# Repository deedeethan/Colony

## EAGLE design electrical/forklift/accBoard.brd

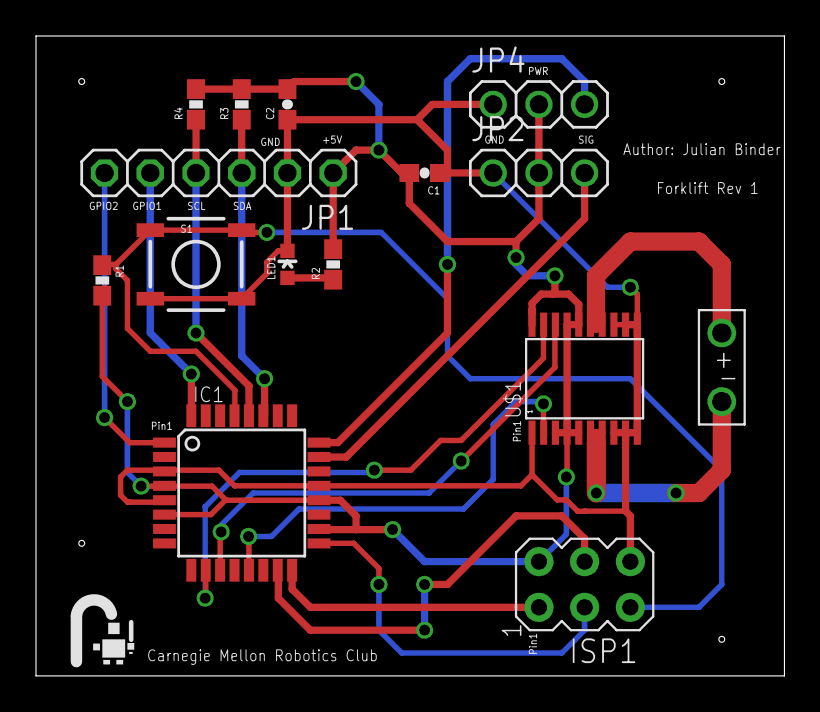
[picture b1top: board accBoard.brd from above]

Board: 2 copper layers, 41.6 x 35.6 mm, 15 parts (0 on the bottom side), 18 nets.

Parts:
C1: 0.1uF; 0603-CAP
C2: 0.1uf; 0603-CAP
IC1: MEGA168; TQFP32-08
ISP1: AVRISP-6; AVRISP
JP1: 1X06
JP2, JP4: 1X03
JP3: 1X02_BIG
LED1: GREENLED; LED-0603
R1, R3, R4: 10K; 0603-RES
R2: 330; 0603-RES
S1: TACTILE_SWITCH_SMD
U$1: TB6593FNG; SSOP20

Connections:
AVR_MISO: IC1.16, ISP1.1
AVR_MOSI: IC1.15, ISP1.4
AVR_RST: IC1.29, ISP1.5, R1.1, S1.1, S1.2
AVR_SCK: IC1.17, ISP1.3
EXTRA_SIG: IC1.24, JP4.3
GND: C1.1, C2.1, IC1.3, IC1.5, IC1.21, ISP1.6, JP1.2, JP2.1, JP4.1, LED1.C, S1.3, S1.4, U$1.1, U$1.8, U$1.9, U$1.10, U$1.11, U$1.12, U$1.13
GPIO1: IC1.32, JP1.5
GPIO2: IC1.1, JP1.6
IN1: IC1.11, U$1.18
IN2: IC1.10, U$1.19
unnamed: LED1.A, R2.1
O1: JP3.P$1, U$1.6, U$1.7
O2: JP3.P$2, U$1.14, U$1.15
POT_SIG: IC1.23, JP2.3
PWM: IC1.13, U$1.2
SCL: IC1.28, JP1.4, R4.1
SDA: IC1.27, JP1.3, R3.1
VCC: C1.2, C2.2, IC1.4, IC1.6, IC1.18, IC1.20, ISP1.2, JP1.1, JP2.2, JP4.2, R1.2, R2.2, R3.2, R4.2, U$1.3, U$1.4, U$1.5, U$1.16, U$1.17, U$1.20

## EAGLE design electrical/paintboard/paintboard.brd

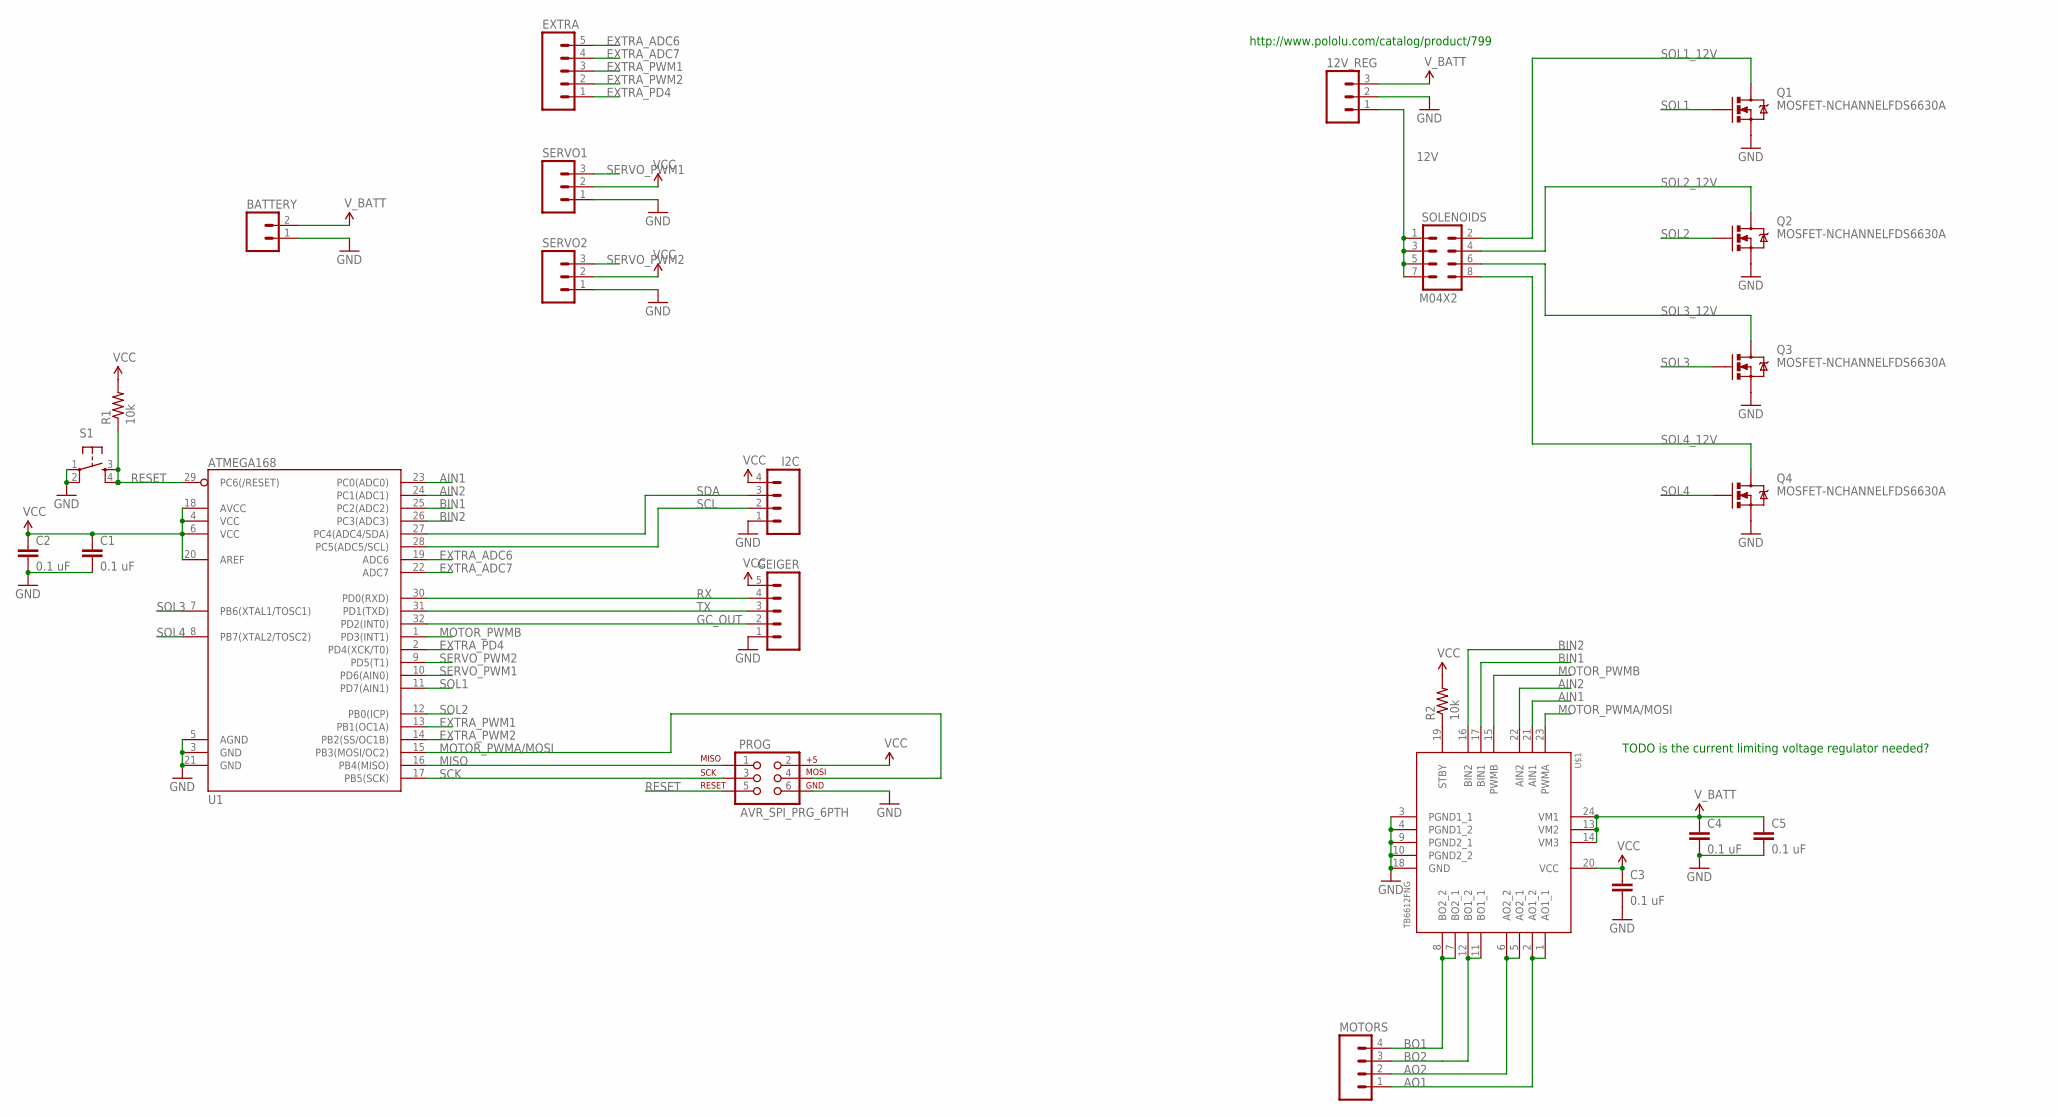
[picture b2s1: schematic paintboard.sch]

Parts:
12V_REG: M03PTH; 1X03
BATTERY: M02PTH; 1X02
C1, C2, C3, C4, C5: 0.1 uF; 0805
EXTRA: M05PTH; 1X05
GEIGER: M05PTH; 1X05
I2C: M04PTH; 1X04
MOTORS: M04PTH; 1X04
PROG: AVR_SPI_PRG_6PTH; 2X3
Q1, Q2, Q3, Q4: MOSFET-NCHANNELFDS6630A; SO08
R1, R2: 10k; 0805
S1: TAC_SWITCHSMD; TACTILE_SWITCH_SMD
SERVO1, SERVO2: M03PTH; 1X03
SOLENOIDS: M04X2; 2X4
U1: ATMEGA168; TQFP32-08
U$1: TB6612FNG; 24-SSOP

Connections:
12V: 12V_REG.1, SOLENOIDS.1, SOLENOIDS.3, SOLENOIDS.5, SOLENOIDS.7
AIN1: U1.23 (PC0(ADC0)), U$1.21 (AIN1)
AIN2: U1.24 (PC1(ADC1)), U$1.22 (AIN2)
AO1: MOTORS.1, U$1.1 (AO1_1), U$1.2 (AO1_2)
AO2: MOTORS.2, U$1.5 (AO2_1), U$1.6 (AO2_2)
BIN1: U1.25 (PC2(ADC2)), U$1.17 (BIN1)
BIN2: U1.26 (PC3(ADC3)), U$1.16 (BIN2)
BO1: MOTORS.4, U$1.7 (BO2_1), U$1.8 (BO2_2)
BO2: MOTORS.3, U$1.11 (BO1_1), U$1.12 (BO1_2)
EXTRA_ADC6: EXTRA.5, U1.19 (ADC6)
EXTRA_ADC7: EXTRA.4, U1.22 (ADC7)
EXTRA_PD4: EXTRA.1, U1.2 (PD4(XCK/T0))
EXTRA_PWM1: EXTRA.3, U1.13 (PB1(OC1A))
EXTRA_PWM2: EXTRA.2, U1.14 (PB2(SS/OC1B))
GC_OUT: GEIGER.2, U1.32 (PD2(INT0))
GND: 12V_REG.2, BATTERY.1, C1.2, C2.2, C3.2, C4.2, C5.2, GEIGER.1, I2C.1, PROG.6, Q1.1 (S), Q1.2 (S), Q1.3 (S), Q2.1 (S), Q2.2 (S), Q2.3 (S), Q3.1 (S), Q3.2 (S), Q3.3 (S), Q4.1 (S), Q4.2 (S), Q4.3 (S), S1.1, S1.2, SERVO1.1, SERVO2.1, U1.3 (GND), U1.5 (AGND), U1.21 (GND), U$1.3 (PGND1_1), U$1.4 (PGND1_2), U$1.9 (PGND2_1), U$1.10 (PGND2_2), U$1.18 (GND)
MISO: PROG.1, U1.16 (PB4(MISO))
MOTOR_PWMA/MOSI: PROG.4, U1.15 (PB3(MOSI/OC2)), U$1.23 (PWMA)
MOTOR_PWMB: U1.1 (PD3(INT1)), U$1.15 (PWMB)
unnamed: R2.1, U$1.19 (STBY)
RESET: PROG.5, R1.1, S1.3, S1.4, U1.29 (PC6(/RESET))
RX: GEIGER.4, U1.30 (PD0(RXD))
SCK: PROG.3, U1.17 (PB5(SCK))
SCL: I2C.2, U1.28 (PC5(ADC5/SCL))
SDA: I2C.3, U1.27 (PC4(ADC4/SDA))
SERVO_PWM1: SERVO1.3, U1.10 (PD6(AIN0))
SERVO_PWM2: SERVO2.3, U1.9 (PD5(T1))
SOL1: Q1.4 (G), U1.11 (PD7(AIN1))
SOL1_12V: Q1.5 (D), Q1.6 (D), Q1.7 (D), Q1.8 (D), SOLENOIDS.2
SOL2: Q2.4 (G), U1.12 (PB0(ICP))
SOL2_12V: Q2.5 (D), Q2.6 (D), Q2.7 (D), Q2.8 (D), SOLENOIDS.4
SOL3: Q3.4 (G), U1.7 (PB6(XTAL1/TOSC1))
SOL3_12V: Q3.5 (D), Q3.6 (D), Q3.7 (D), Q3.8 (D), SOLENOIDS.6
SOL4: Q4.4 (G), U1.8 (PB7(XTAL2/TOSC2))
SOL4_12V: Q4.5 (D), Q4.6 (D), Q4.7 (D), Q4.8 (D), SOLENOIDS.8
TX: GEIGER.3, U1.31 (PD1(TXD))
VCC: C1.1, C2.1, C3.1, GEIGER.5, I2C.4, PROG.2, R1.2, R2.2, SERVO1.2, SERVO2.2, U1.4 (VCC), U1.6 (VCC), U1.18 (AVCC), U1.20 (AREF), U$1.20 (VCC)
V_BATT: 12V_REG.3, BATTERY.2, C4.1, C5.1, U$1.13 (VM2), U$1.14 (VM3), U$1.24 (VM1)

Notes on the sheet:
http://www.pololu.com/catalog/product/799
TODO is the current limiting voltage regulator needed?

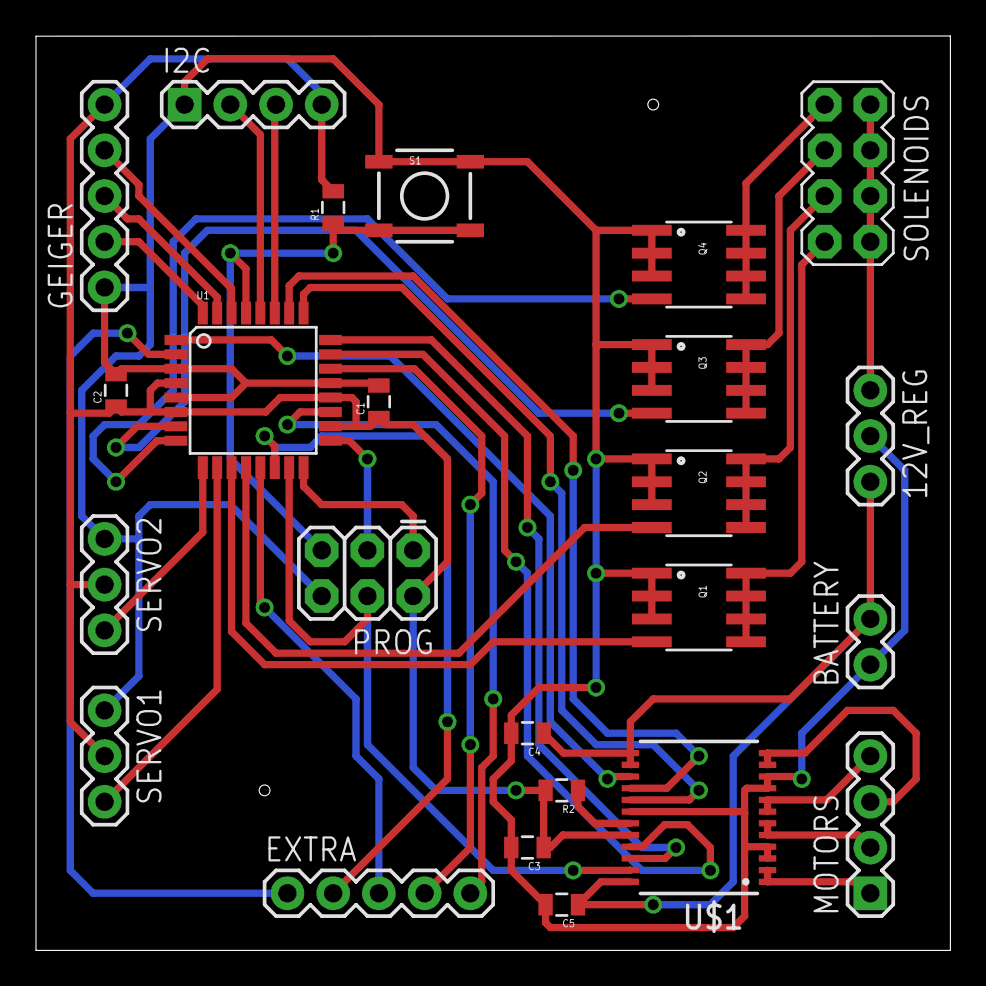
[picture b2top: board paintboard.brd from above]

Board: 2 copper layers, 50.8 x 50.8 mm, 24 parts (0 on the bottom side), 38 nets.

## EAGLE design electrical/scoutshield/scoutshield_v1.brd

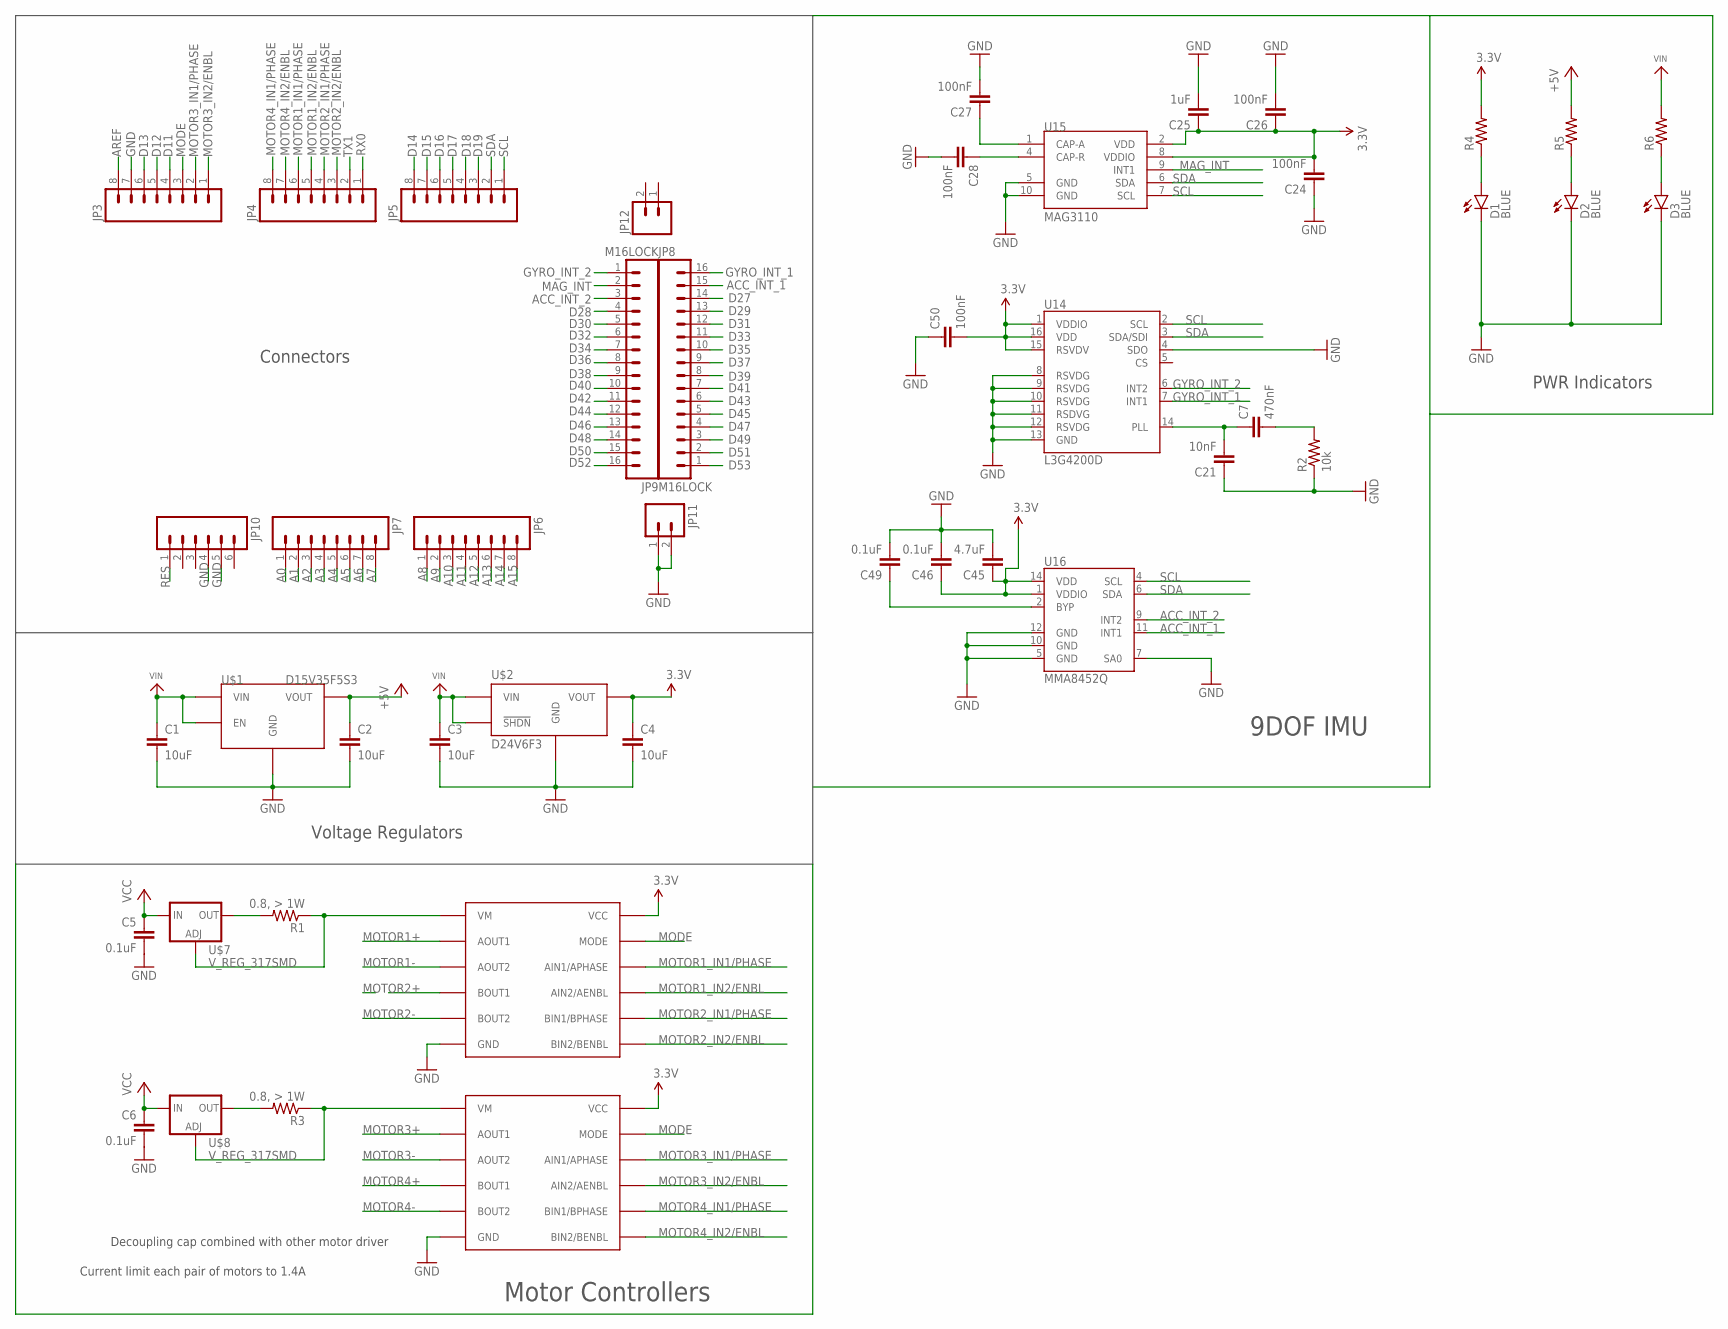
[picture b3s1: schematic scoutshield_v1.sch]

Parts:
C1, C2, C3, C4: 10uF; 1206
C5, C6, C46, C49: 0.1uF; 0603-CAP
C7: 470nF; 0603-CAP
C21: 10nF; 0603-CAP
C24, C26, C27, C28, C50: 100nF; 0603-CAP
C25: 1uF; 0603-CAP
C45: 4.7uF; 0603-CAP
D1, D2, D3: BLUE; LED-0603
JP3, JP4, JP5, JP6, JP7: M08LOCK; 1X08_LOCK
JP8, JP9: M16LOCK; 1X16_LOCK
JP10: M06LOCK; 1X06_LOCK
JP11, JP12: M02LOCK; 1X02_LOCK
R1, R3: 0.8, > 1W; R2512
R2: 10k; R0603
R4, R5, R6: RESISTOR0603-RES; 0603-RES
U14: L3G4200D; LGA16-4X4
U15: MAG3110; DFN-10
U16: MMA8452Q; QFN-16_0.5MM
U$1: D15V35F5S3
U$2: D24V6F3
U$5, U$6: DRV8835; WSON-12
U$7, U$8: V_REG_317SMD; SOT223

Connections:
3.3V: C4.1, C24.2, C25.1, C26.1, C45.1, C46.1, C50.2, R4.2, U14.1 (VDDIO), U14.15 (RSVDV), U14.16 (VDD), U15.2 (VDD), U15.8 (VDDIO), U16.1 (VDDIO), U16.14 (VDD), U$2.VOUT, U$5.P12 (VCC), U$6.P12 (VCC)
+5V: C2.1, R5.2, U$1.VOUT
A0: JP7.1
A1: JP7.2
A2: JP7.3
A3: JP7.4
A4: JP7.5
A5: JP7.6
A6: JP7.7
A7: JP7.8
A8: JP6.1
A9: JP6.2
A10: JP6.3
A11: JP6.4
A12: JP6.5
A13: JP6.6
A14: JP6.7
A15: JP6.8
ACC_INT_1: JP8.15, U16.11 (INT1)
ACC_INT_2: JP9.3, U16.9 (INT2)
AREF: JP3.8
D11: JP3.4
D12: JP3.5
D13: JP3.6
D14: JP5.8
D15: JP5.7
D16: JP5.6
D17: JP5.5
D18: JP5.4
D19: JP5.3
D27: JP8.14
D28: JP9.4
D29: JP8.13
D30: JP9.5
D31: JP8.12
D32: JP9.6
D33: JP8.11
D34: JP9.7
D35: JP8.10
D36: JP9.8
D37: JP8.9
D38: JP9.9
D39: JP8.8
D40: JP9.10
D41: JP8.7
D42: JP9.11
D43: JP8.6
D44: JP9.12
D45: JP8.5
D46: JP9.13
D47: JP8.4
D48: JP9.14
D49: JP8.3
D50: JP9.15
D51: JP8.2
D52: JP9.16
D53: JP8.1
GND: C1.2, C2.2, C3.2, C4.2, C5.2, C6.2, C21.1, C24.1, C25.2, C26.2, C27.2, C28.2, C45.2, C46.2, C49.2, C50.1, D1.C, D2.C, D3.C, JP3.7, JP10.4, JP10.5, JP11.1, JP11.2, R2.1, U14.4 (SDO), U14.8 (RSVDG), U14.9 (RSVDG), U14.10 (RSVDG), U14.11 (RSDVG), U14.12 (RSVDG), U14.13 (GND), U15.5 (GND), U15.10 (GND), U16.5 (GND), U16.7 (SA0), U16.10 (GND), U16.12 (GND), U$1.GND1 (GND), U$1.GND2 (GND), U$2.GND, U$5.P6 (GND), U$5.THERM1 (GND), U$5.THERM2 (GND), U$5.THERM3 (GND), U$5.THERM4 (GND), U$5.THERMCENTER (GND), U$6.P6 (GND), U$6.THERM1 (GND), U$6.THERM2 (GND), U$6.THERM3 (GND), U$6.THERM4 (GND), U$6.THERMCENTER (GND)
GYRO_INT_1: JP8.16, U14.7 (INT1)
GYRO_INT_2: JP9.1, U14.6 (INT2)
MAG_INT: JP9.2, U15.9 (INT1)
MODE: JP3.3, U$5.P11 (MODE), U$6.P11 (MODE)
MOTOR1+: U$6.P2 (AOUT1)
MOTOR1-: U$6.P3 (AOUT2)
MOTOR1_IN1/PHASE: JP4.6, U$6.P10 (AIN1/APHASE)
MOTOR1_IN2/ENBL: JP4.5, U$6.P9 (AIN2/AENBL)
MOTOR2+: U$6.P4 (BOUT1)
MOTOR2-: U$6.P5 (BOUT2)
MOTOR2_IN1/PHASE: JP4.4, U$6.P8 (BIN1/BPHASE)
MOTOR2_IN2/ENBL: JP4.3, U$6.P7 (BIN2/BENBL)
MOTOR3+: U$5.P2 (AOUT1)
MOTOR3-: U$5.P3 (AOUT2)
MOTOR3_IN1/PHASE: JP3.2, U$5.P10 (AIN1/APHASE)
MOTOR3_IN2/ENBL: JP3.1, U$5.P9 (AIN2/AENBL)
MOTOR4+: U$5.P4 (BOUT1)
MOTOR4-: U$5.P5 (BOUT2)
MOTOR4_IN1/PHASE: JP4.8, U$5.P8 (BIN1/BPHASE)
MOTOR4_IN2/ENBL: JP4.7, U$5.P7 (BIN2/BENBL)
unnamed: R1.1, U$6.P1 (VM), U$7.1 (ADJ)
unnamed: R1.2, U$7.2 (OUT)
unnamed: R3.1, U$5.P1 (VM), U$8.1 (ADJ)
unnamed: R3.2, U$8.2 (OUT)
unnamed: D1.A, R4.1
unnamed: D2.A, R5.1
unnamed: D3.A, R6.1
unnamed: C7.1, C21.2, U14.14 (PLL)
unnamed: C7.2, R2.2
unnamed: C49.1, U16.2 (BYP)
unnamed: C27.1, U15.1 (CAP-A)
unnamed: C28.1, U15.4 (CAP-R)
RES: JP10.1
RX0: JP4.1
SCL: JP5.1, U14.2 (SCL), U15.7 (SCL), U16.4 (SCL)
SDA: JP5.2, U14.3 (SDA/SDI), U15.6 (SDA), U16.6 (SDA)
TX1: JP4.2
VIN: C1.1, C3.1, C5.1, C6.1, R6.2, U$1.EN, U$1.VIN, U$2.!SHDN, U$2.VIN, U$7.3 (IN), U$8.3 (IN)

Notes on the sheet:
Connectors
Voltage Regulators
9DOF IMU
Decoupling cap combined with other motor driver
Current limit each pair of motors to 1.4A
Motor Controllers
PWR Indicators

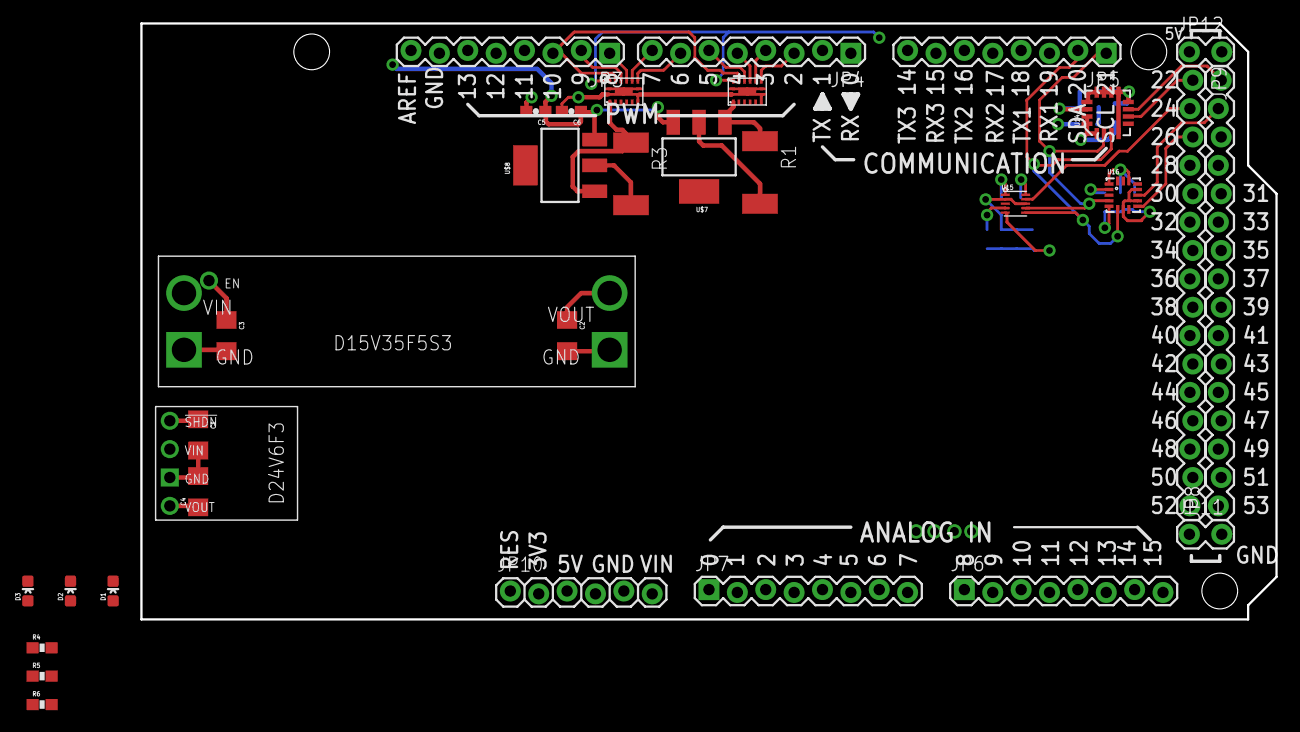
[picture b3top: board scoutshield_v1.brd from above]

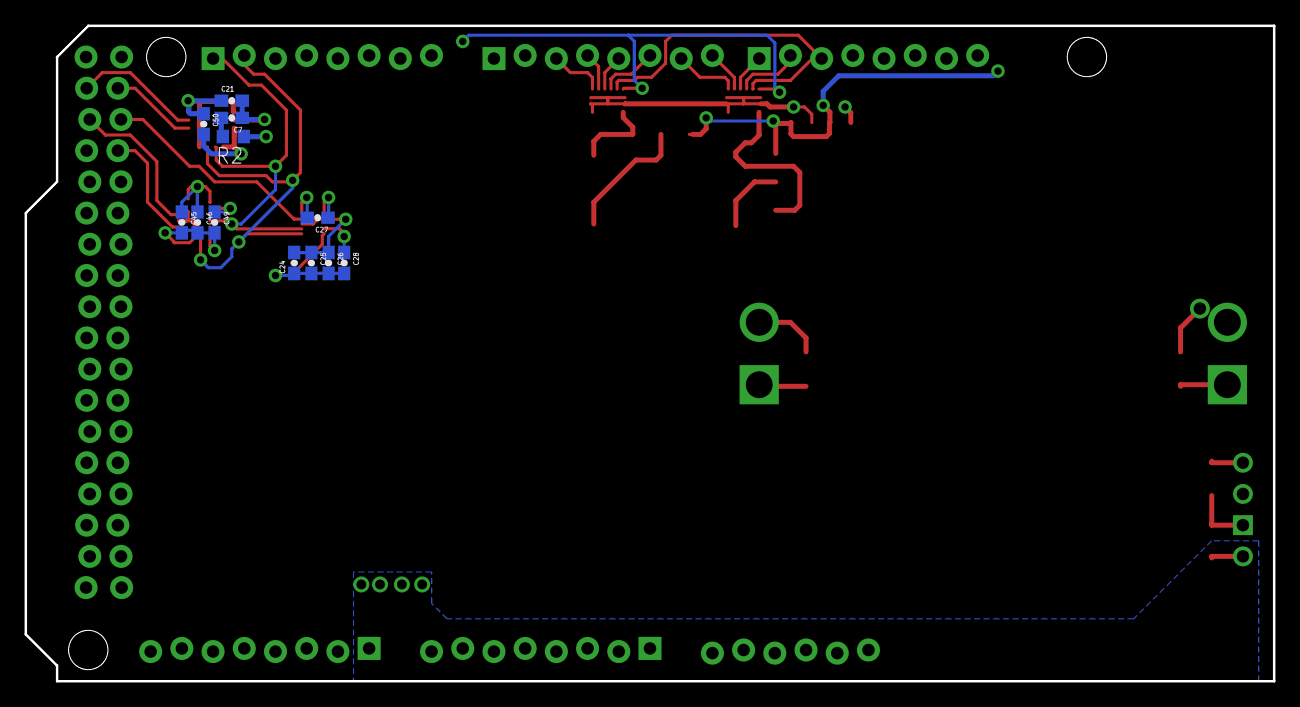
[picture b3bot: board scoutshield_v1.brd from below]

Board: 4 copper layers, 101.6 x 53.3 mm, 45 parts (12 on the bottom side), 32 nets.

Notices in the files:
parts and their libraries:
SparkFun-DigitalIC: Licensing: CC v3.0 Share-Alike You are welcome to use this library for commercial purposes.
SparkFun-LED: Licensing: Creative Commons ShareAlike 4.0 International - https://creativecommons.org/licenses/by-sa/4.0
